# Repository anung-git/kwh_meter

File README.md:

<h1> KWH METER DIGITAL </h1>
<h2> nodemcu - blynk </h2>

Monitoring Kwh menggunakan modul pzem-004t-v3 & modul NodeMCU ditampilkan pada dasboard blynk

refreensi <br>
https://github.com/pkarun/Blynk-PZEM-004T-3-Phase-Failure-Automation <br>
https://github.com/pkarun/Blynk-PZEM-004T-v3.0-Multiple-device

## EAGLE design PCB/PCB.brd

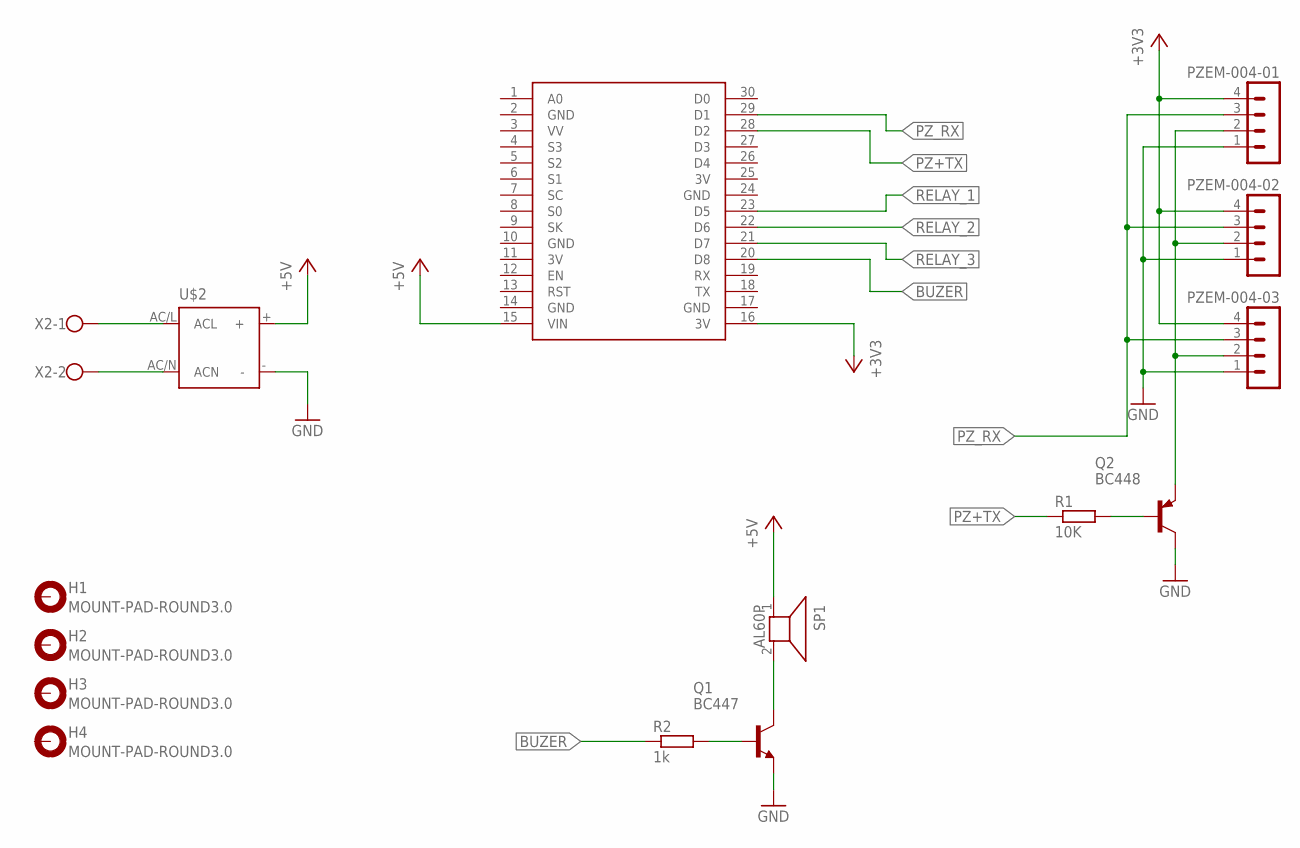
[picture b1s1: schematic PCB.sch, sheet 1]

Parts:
H1, H2, H3, H4: MOUNT-PAD-ROUND3.0; 3,0-PAD
PZEM-004-01, PZEM-004-02, PZEM-004-03: MA04-1
Q1: BC447; TO92-EBC
Q2: BC448; TO92-EBC
R1: 10K; 0207/10
R2: 1k; 0207/10
SP1: AL60P
U$1: NODEMCU
U$2: PM-05
X2: W237-102

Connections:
3V: U$1.11 (3V), U$1.25 (3V)
+3V3: PZEM-004-01.4, PZEM-004-02.4, PZEM-004-03.4, U$1.16 (3V)
+5V: SP1.1, U$1.15 (VIN), U$2.+; also elsewhere on the board
BUZER: R2.1, U$1.20 (D8)
GND: PZEM-004-01.1, PZEM-004-02.1, PZEM-004-03.1, Q1.E, Q2.C, U$1.2 (GND), U$1.10 (GND), U$1.14 (GND), U$1.17 (GND), U$1.24 (GND), U$2.-; also elsewhere on the board
unnamed: Q1.C, SP1.2
unnamed: Q1.B, R2.2
unnamed: Q2.B, R1.2
unnamed: PZEM-004-01.2, PZEM-004-02.2, PZEM-004-03.2, Q2.E
unnamed: U$2.AC/N (ACN), X2.2
unnamed: U$2.AC/L (ACL), X2.1
PZ+TX: R1.1, U$1.28 (D2)
PZ_RX: PZEM-004-01.3, PZEM-004-02.3, PZEM-004-03.3, U$1.29 (D1)
RELAY_1: U$1.23 (D5); also elsewhere on the board
RELAY_2: U$1.22 (D6); also elsewhere on the board
RELAY_3: U$1.21 (D7); also elsewhere on the board

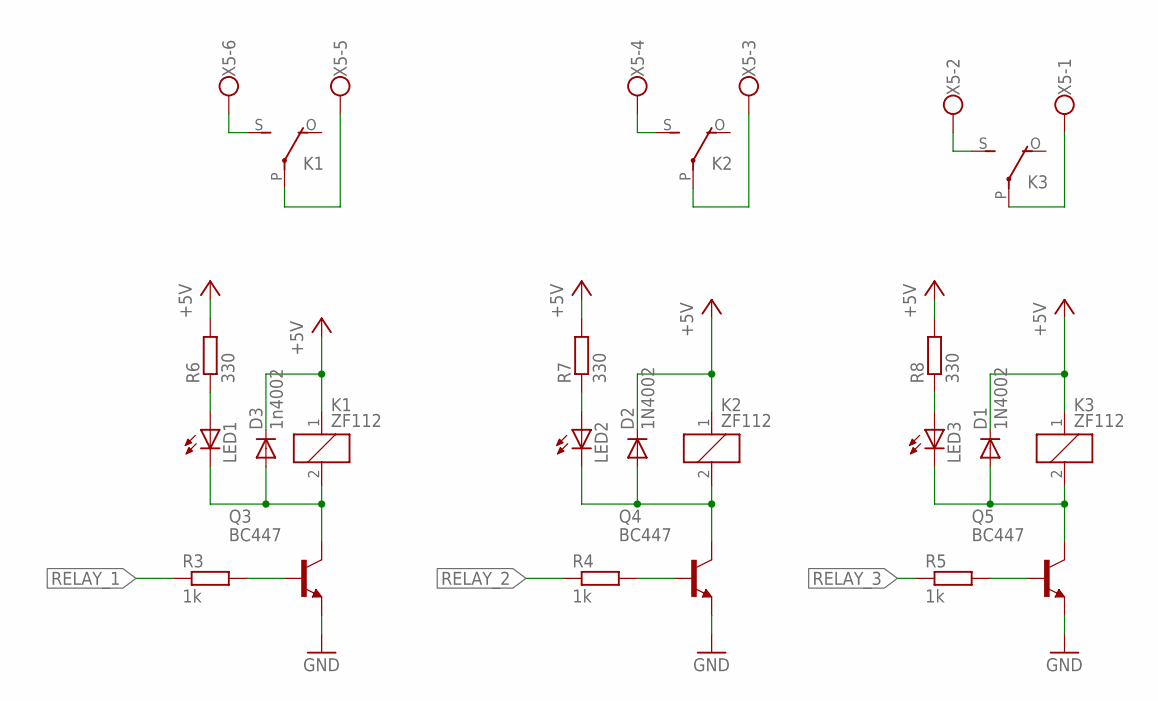
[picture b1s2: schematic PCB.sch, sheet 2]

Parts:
D1, D2: 1N4002; DO35-10
D3: 1n4002; DO35-10
K1, K2, K3: ZF112
LED1, LED2, LED3: LED5MM
Q3, Q4, Q5: BC447; TO92-EBC
R3, R4, R5: 1k; 0207/10
R6, R7, R8: 330; 0207/10
X5: W237-6

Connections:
+5V: D1.C, D2.C, D3.C, K1.1, K2.1, K3.1, R6.2, R7.2, R8.2; also elsewhere on the board
GND: Q3.E, Q4.E, Q5.E; also elsewhere on the board
unnamed: D3.A, K1.2, LED1.K (C), Q3.C
unnamed: Q3.B, R3.2
unnamed: D2.A, K2.2, LED2.K (C), Q4.C
unnamed: Q4.B, R4.2
unnamed: K3.S, X5.2
unnamed: Q5.B, R5.2
unnamed: LED1.A, R6.1
unnamed: K3.P, X5.1
unnamed: LED2.A, R7.1
unnamed: LED3.A, R8.1
unnamed: D1.A, K3.2, LED3.K (C), Q5.C
unnamed: K2.P, X5.3
unnamed: K2.S, X5.4
unnamed: K1.P, X5.5
unnamed: K1.S, X5.6
RELAY_1: R3.1; also elsewhere on the board
RELAY_2: R4.1; also elsewhere on the board
RELAY_3: R5.1; also elsewhere on the board

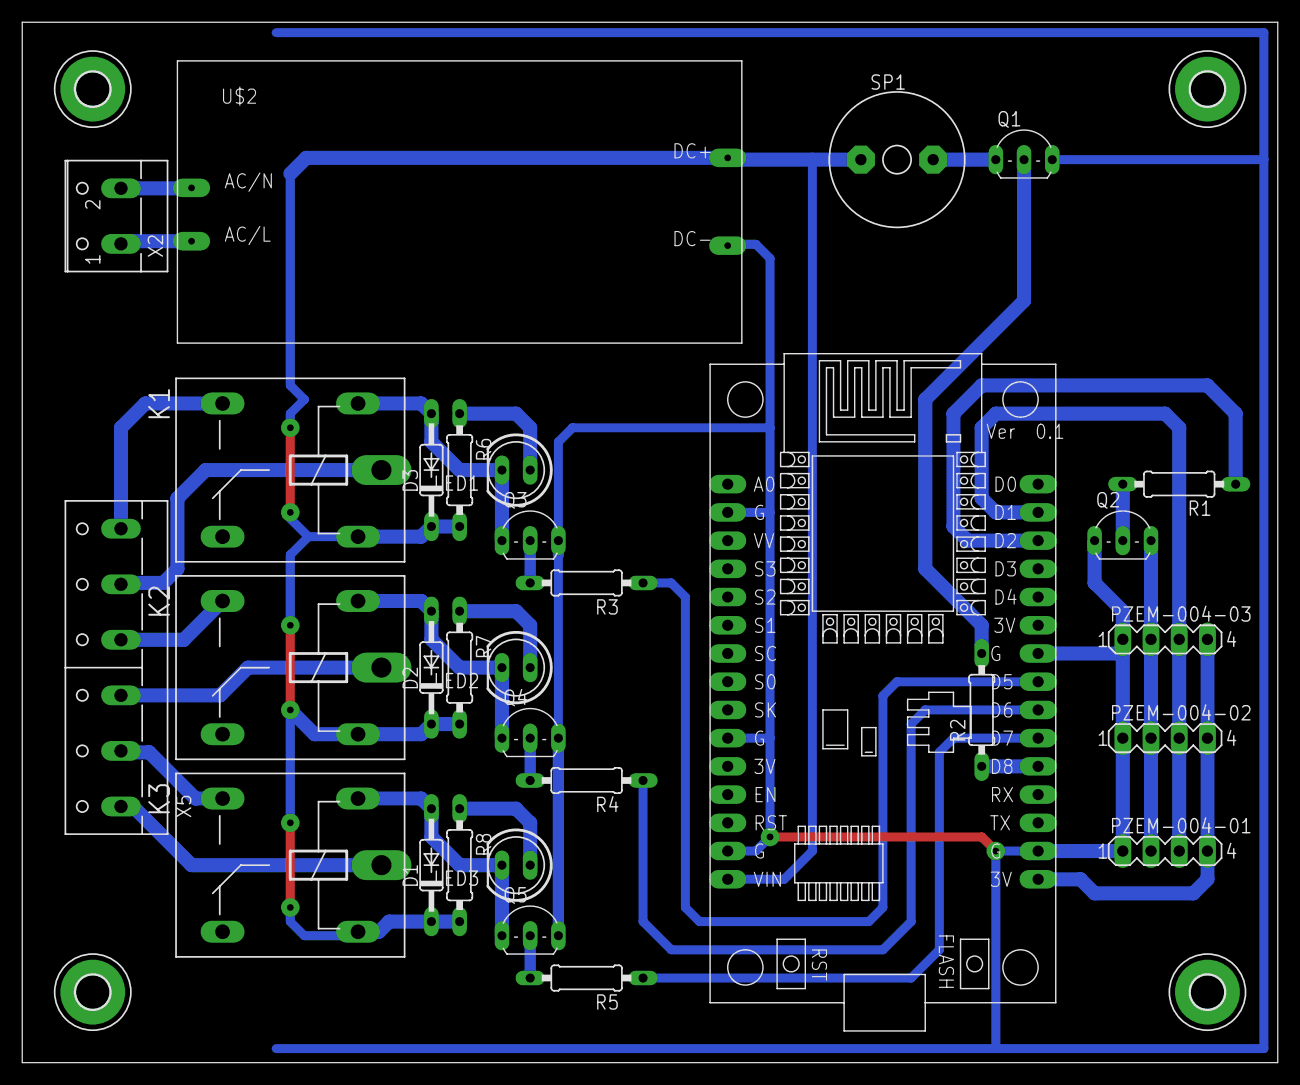
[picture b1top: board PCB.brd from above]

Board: 2 copper layers, 113.0 x 93.7 mm, 34 parts (0 on the bottom side), 31 nets.

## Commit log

2019-12-29 kwh metter
2019-12-29 buat fungsi baca pzem
2020-01-12 finish

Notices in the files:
parts and their libraries:
SparkFun-Aesthetics: Licensing: Creative Commons ShareAlike 4.0 International - https://creativecommons.org/licenses/by-sa/4.0
